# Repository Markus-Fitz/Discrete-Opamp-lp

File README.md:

# Discrete-Opamp
 Discrete OpAmp for low voltage, low power audio applications.

# Specs
 The BC557- and BC547-transistors limit the opamp to 45V supply voltage. The OpAmp is intended for low-power amplification, the end-stage is limited to source and sink a maximum of 10mA. The OpAmp operates entirely in class A. The footprint is that of a standard single OpAmp in a DIP8-package.

Simulation of the OpAmp indicates a THD of 0.000042% at 1kHz with 2Vpp into 100kOhm. This is probably unrealistic, but an indication of good operation. The open-loop gain resulted in around 108dB.

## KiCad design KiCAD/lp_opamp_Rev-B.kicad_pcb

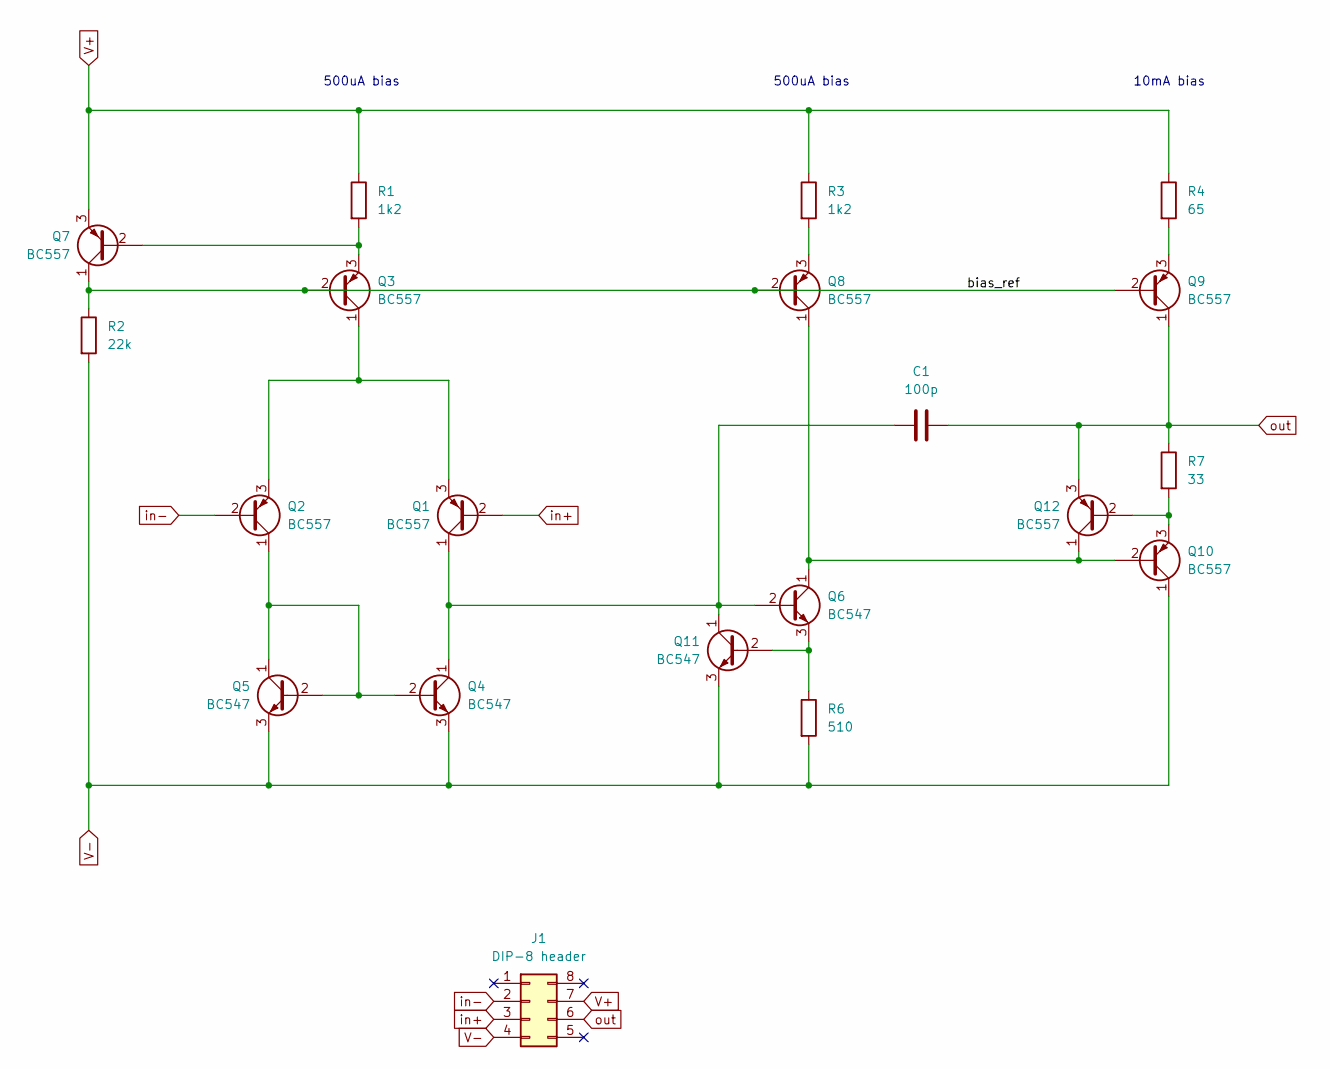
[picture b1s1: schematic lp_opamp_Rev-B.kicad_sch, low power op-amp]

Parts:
C1: 100p; C_Disc_D5.0mm_W2.5mm_P2.50mm
J1: DIP-8 header; DIP-8_W7.62mm_Socket
Q1, Q2, Q3, Q7, Q8, Q9, Q10, Q12: BC557; TO-92_Inline_Wide
Q4, Q5, Q6, Q11: BC547; TO-92_Inline_Wide
R1, R3: 1k2; resistor_symm
R2: 22k; resistor_symm
R4: 65; resistor_symm
R6: 510; resistor_symm
R7: 33; resistor_symm

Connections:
/bias_ref: Q3.2 (B), Q7.1 (C), Q8.2 (B), Q9.2 (B), R2.1
unnamed: C1.1, Q1.1 (C), Q4.1 (C), Q6.2 (B), Q11.1 (C)
unnamed: Q1.3 (E), Q2.3 (E), Q3.1 (C)
unnamed: Q2.1 (C), Q4.2 (B), Q5.1 (C), Q5.2 (B)
unnamed: Q3.3 (E), Q7.2 (B), R1.2
unnamed: Q8.3 (E), R3.2
unnamed: Q9.3 (E), R4.2
unnamed: Q6.1 (C), Q8.1 (C), Q10.2 (B), Q12.1 (C)
unnamed: Q10.3 (E), Q12.2 (B), R7.2
unnamed: Q6.3 (E), Q11.2 (B), R6.1
V+: J1.7, Q7.3 (E), R1.1, R3.1, R4.1
V-: J1.4, Q4.3 (E), Q5.3 (E), Q10.1 (C), Q11.3 (E), R2.2, R6.2
in+: J1.3, Q1.2 (B)
in-: J1.2, Q2.2 (B)
out: C1.2, J1.6, Q9.1 (C), Q12.3 (E), R7.1

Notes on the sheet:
500uA bias
10mA bias

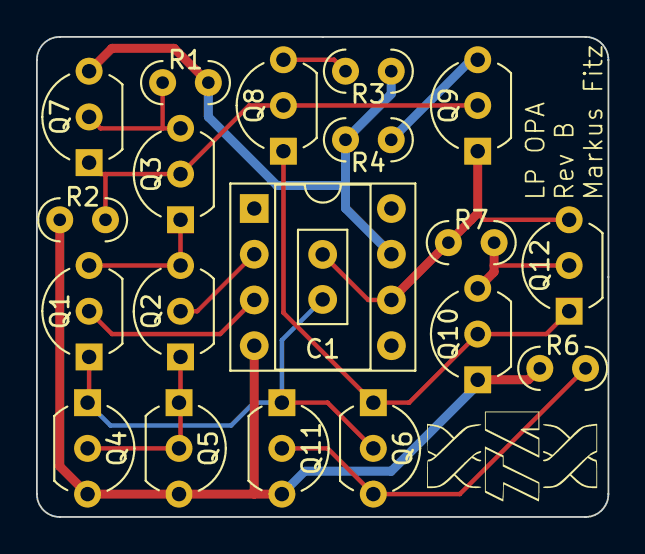
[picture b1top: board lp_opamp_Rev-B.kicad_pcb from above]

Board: 2 copper layers, 31.8 x 26.7 mm, 20 parts (0 on the bottom side), 15 nets.

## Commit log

2024-04-07 Initial Commit.
    Initial commit
2024-04-07 Updated Readme.
    Addition of specs to Readme.
2024-04-07 Create LICENSE
    Addition of GNU-License.
2024-04-07 Addition of rendering.
    Addition of rendering from top-side of OpAmp done in KiCAD.
2026-05-19 Update README.md
    Added rendering of the opamp in the README.
2026-05-19 Update README.md
    Resizing of rendering.
2026-05-19 Update README.md
    Reformatting.
